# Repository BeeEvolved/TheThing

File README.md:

# portal-hardware -TheThing fork
**TheThing fork goals**:

   - add USB-C
   - add easy to drop in OLED Yellow and Blue Screen

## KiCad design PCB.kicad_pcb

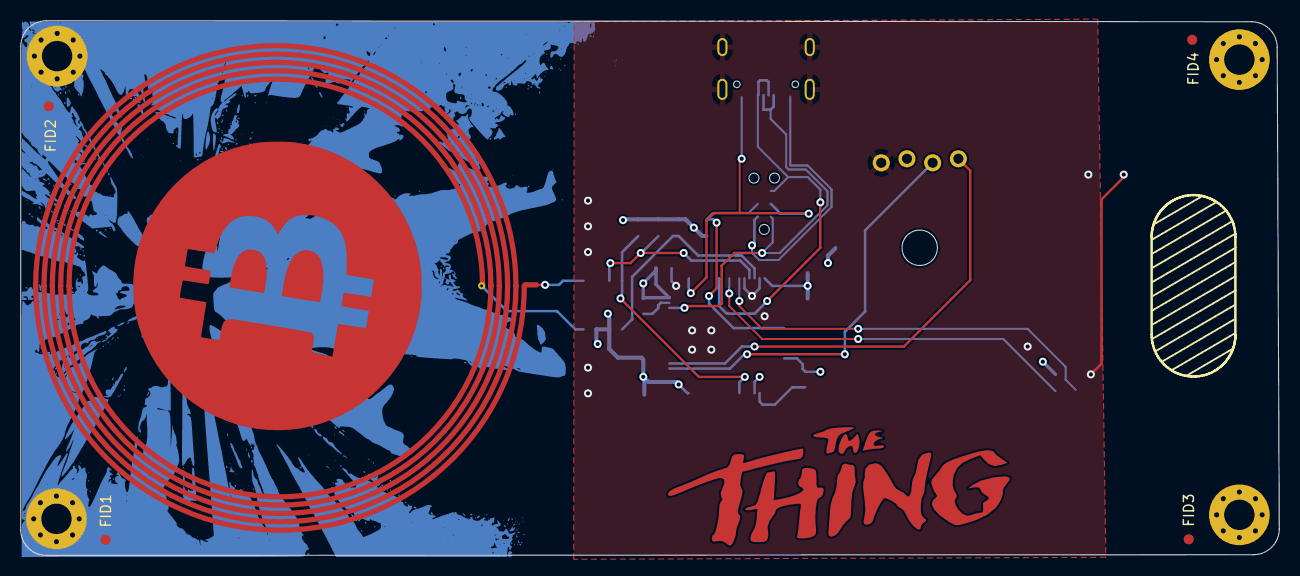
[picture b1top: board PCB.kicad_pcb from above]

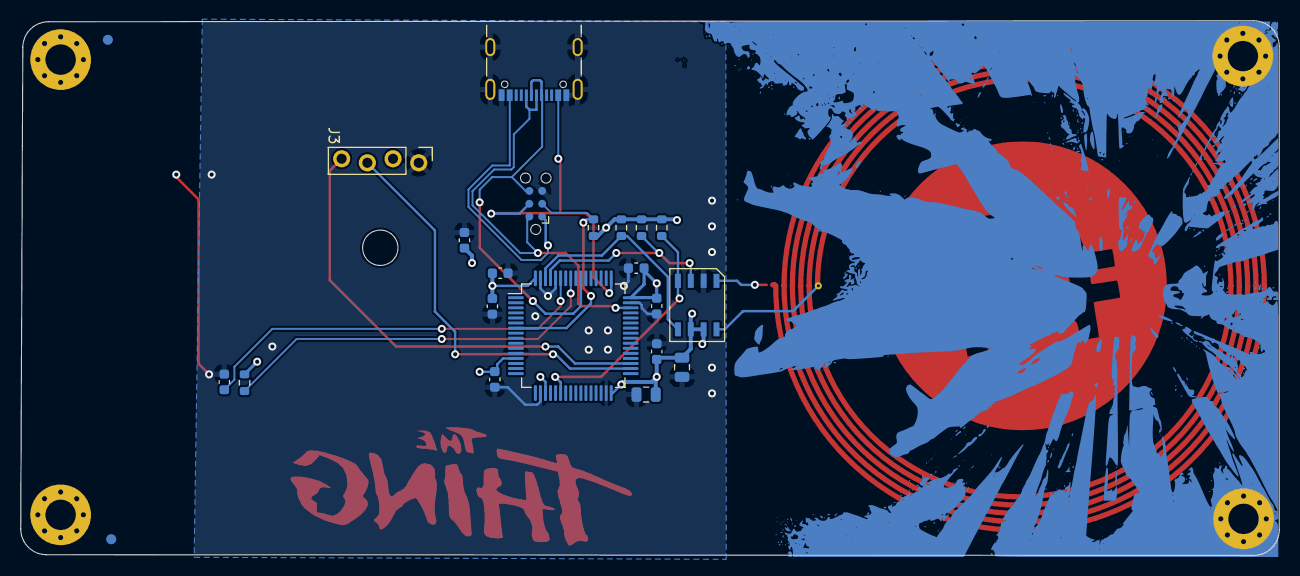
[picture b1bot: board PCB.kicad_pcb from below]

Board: 4 copper layers, 124.4 x 52.9 mm, 35 parts (25 on the bottom side), 16 nets.

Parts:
A1: Antenna; Antenna-Round-13.8MHz-53pF-Class3-50mm
A2: TSC; TSC-Rectangle-25x16mm
C1, C9: 4.7u; C_0805_2012Metric
C2, C3, C4, C5, C6, C8: 100n; C_0603_1608Metric
C14: 22n; C_0603_1608Metric
C17: 1u; C_0603_1608Metric
FID1, FID2, FID3, FID4, FID5, FID6, FID7, FID8: Fiducial; Fiducial_1mm_Mask2mm
H7, H8#2, H9, H10: MountingHole_Pad; MountingHole_3mm_Pad_Via
H8: MountingHole; MountingHole_3.5mm
J1: Conn_ARM_SWD_TagConnect_TC2030; Tag-Connect_TC2030-IDC-NL_2x03_P1.27mm_Vertical
J3: Conn_01x04; PinHeader_1x04_P2.54mm_Vertical_shifted
J8: USB_C_Receptacle_USB2.0; USB_C_Receptacle_GCT_USB4105-xx-A_16P_TopMnt_Horizontal
R1, R2, R3, R10: 10k; R_0603_1608Metric
R8: 1k; R_0603_1608Metric
U2: STM32L476RGTx; LQFP-64_10x10mm_P0.5mm
U3: NT3H2X11; SOT96-1

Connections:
DISP_SCL: J3.3, U2.34 (PB13)
DISP_SDA: J3.4, U2.35 (PB14)
GND: A2.2 (SHLD), C1.2, C2.2, C3.2, C4.2, C5.2, C6.2, C8.2, C9.2, C14.1, C17.2, H7.1, H8#2.1, H9.1, H10.1, J1.5 (GND), J3.1, J8.A1 (GND), J8.A12 (GND), J8.B1 (GND), J8.B12 (GND), J8.S1 (SHIELD), U2.12 (VSSA), U2.18 (VSS), U2.31 (VSS), U2.47 (VSS), U2.60 (BOOT0), U2.63 (VSS), U3.2 (VSS)
NFC_INT: R3.1, U2.22 (PA6), U3.4 (FD)
NFC_SCL: R2.1, U2.61 (PB8), U3.3 (SCL)
NFC_SDA: R1.1, U2.62 (PB9), U3.5 (SDA)
NRST: J1.3 (~RESET), R10.2, U2.7 (NRST)
unnamed: A1.1 (A), U3.8 (LB)
unnamed: A1.2 (B), U3.1 (LA)
unnamed: A2.1 (BTN), R8.2
SWCLK: J1.4 (SWCLK), J8.A4 (VBUS), J8.B9 (VBUS), U2.49 (PA14)
SWDIO: J1.2 (SWDIO), J8.A6 (D+), J8.B6 (D+), U2.46 (PA13)
SWO: J1.6 (SWO), J8.A7 (D-), J8.B7 (D-), U2.55 (PB3)
TSC_G2_IO2: R8.1, U2.57 (PB5)
TSC_G2_IO4: C14.2, U2.59 (PB7)
VCC: C1.1, C2.1, C3.1, C4.1, C5.1, C6.1, C8.1, C9.1, C17.1, J1.1 (VCC), J3.2, J8.A9 (VBUS), J8.B4 (VBUS), R1.2, R2.2, R3.2, R10.1, U2.13 (VDDA), U2.19 (VDD), U2.32 (VDD), U2.48 (VDDUSB), U2.64 (VDD), U3.6 (VCC), U3.7 (VOUT)

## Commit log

2024-06-07 TheThing PCB
2024-06-07 TheThing pretty
